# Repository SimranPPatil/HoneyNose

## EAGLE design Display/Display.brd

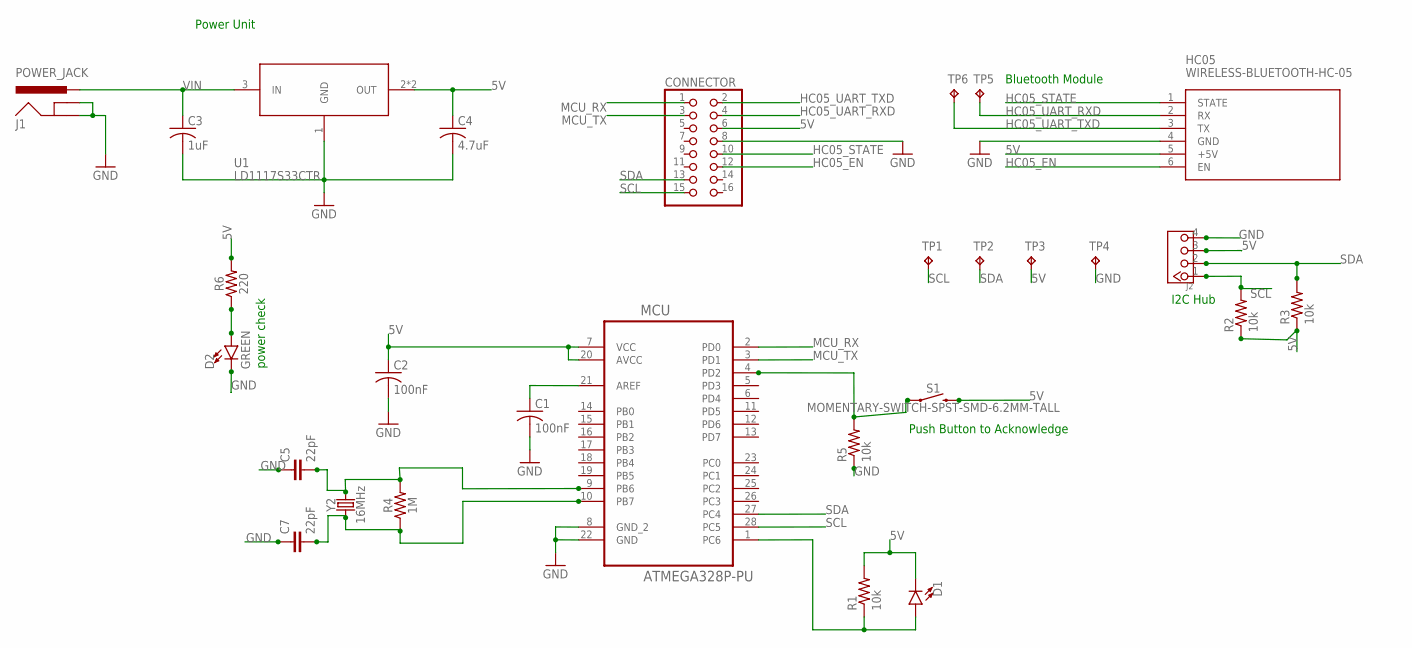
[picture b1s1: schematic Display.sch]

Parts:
C1, C2: 100nF; C0603
C3: 1uF; C0603
C4: 4.7uF; C0603
C5, C7: 22pF; 0603
CONNECTOR: PINHD-2X8; 2X08
D1: LED1206; LED-1206
D2: GREEN; LED-1206
HC05: WIRELESS-BLUETOOTH-HC-05
J1: POWER_JACK; POWER_JACK_PTH
J2: TWIG-4P-2.0; 4P-2.0-W/O-BUCKLE
MCU: ATMEGA328P-PU; DIP254P762X457-28
R1, R2, R3, R5: 10k; R0603
R4: 1M; 0603
R6: 220; 0603
S1: MOMENTARY-SWITCH-SPST-SMD-6.2MM-TALL; TACTILE_SWITCH_SMD_6.2MM_TALL
TP1, TP2, TP3, TP4, TP5, TP6: TPTP20R; TP20R
U1: LD1117S33CTR; SOT223
Y2: 16MHz; HC49US

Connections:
5V: C2.1, C4.1, CONNECTOR.6, D1.C, HC05.5 (+5V), J2.3, MCU.7 (VCC), MCU.20 (AVCC), R1.2, R2.1, R3.1, R6.2, S1.B2 (2), TP3.TP, U1.2 (OUT), U1.4 (OUT)
GND: C1.2, C2.2, C3.2, C4.2, C5.1, C7.1, CONNECTOR.8, D2.C, HC05.4 (GND), J1.GND, J1.GNDBREAK, J2.4, MCU.8 (GND_2), MCU.22 (GND), R5.1, TP4.TP, U1.1 (GND)
HC05_EN: CONNECTOR.12, HC05.6 (EN)
HC05_STATE: CONNECTOR.10, HC05.1 (STATE)
HC05_UART_RXD: CONNECTOR.4, HC05.2 (RX), TP5.TP
HC05_UART_TXD: CONNECTOR.2, HC05.3 (TX), TP6.TP
MCU_RX: CONNECTOR.1, MCU.2 (PD0)
MCU_TX: CONNECTOR.3, MCU.3 (PD1)
unnamed: C5.2, MCU.9 (PB6), R4.2, Y2.2
unnamed: C1.1, MCU.21 (AREF)
unnamed: C7.2, MCU.10 (PB7), R4.1, Y2.1
unnamed: D1.A, MCU.1 (PC6), R1.1
unnamed: MCU.4 (PD2), R5.2, S1.A2 (1)
unnamed: D2.A, R6.1
SCL: CONNECTOR.15, J2.1, MCU.28 (PC5), R2.2, TP1.TP
SDA: CONNECTOR.13, J2.2, MCU.27 (PC4), R3.2, TP2.TP
VIN: C3.1, J1.PWR, U1.3 (IN)

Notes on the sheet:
Bluetooth Module
Power Unit
power check
I2C Hub
Push Button to Acknowledge

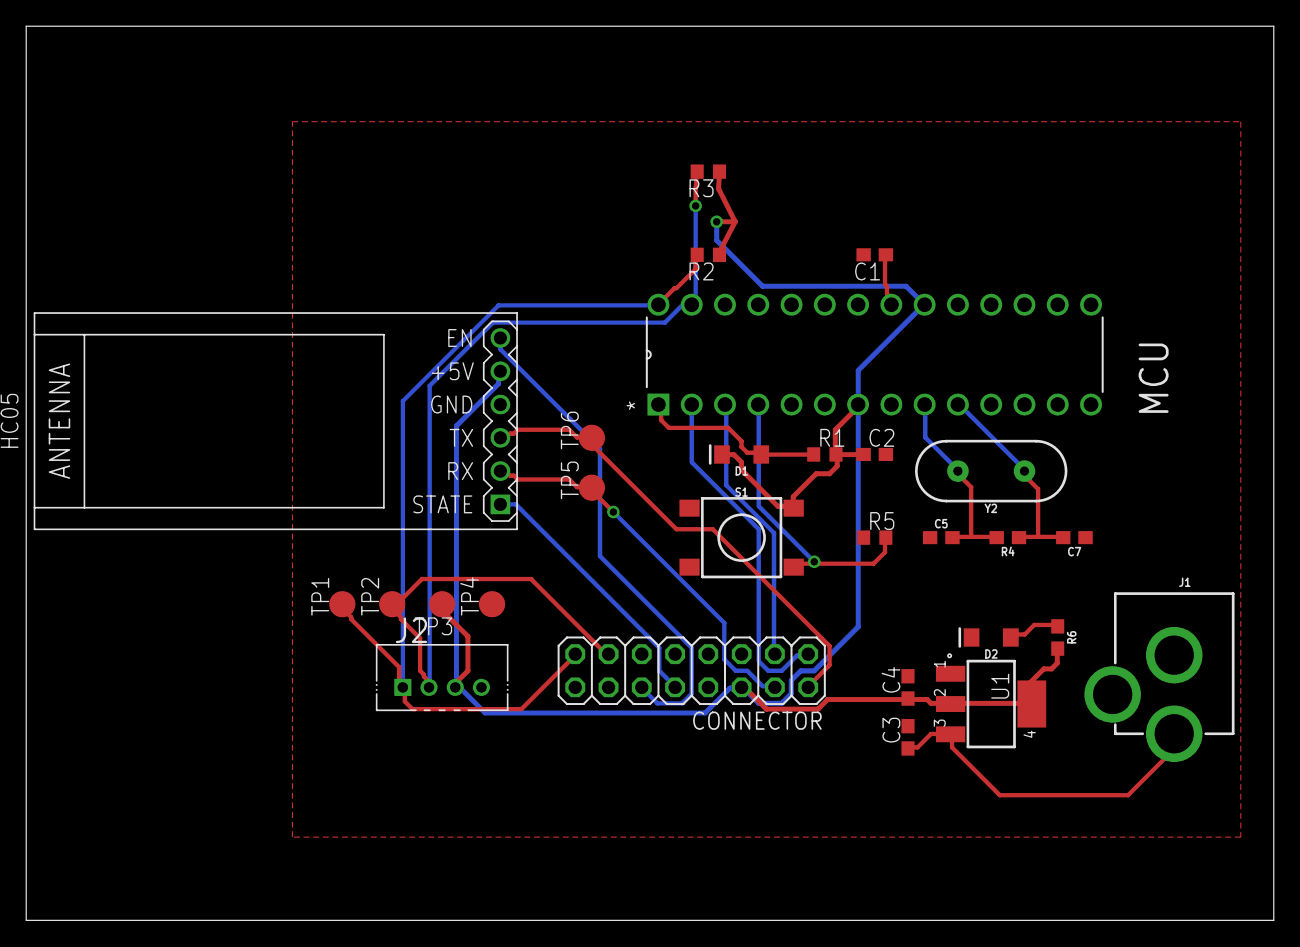
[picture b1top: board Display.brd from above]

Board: 2 copper layers, 95.2 x 68.2 mm, 28 parts (0 on the bottom side), 17 nets.

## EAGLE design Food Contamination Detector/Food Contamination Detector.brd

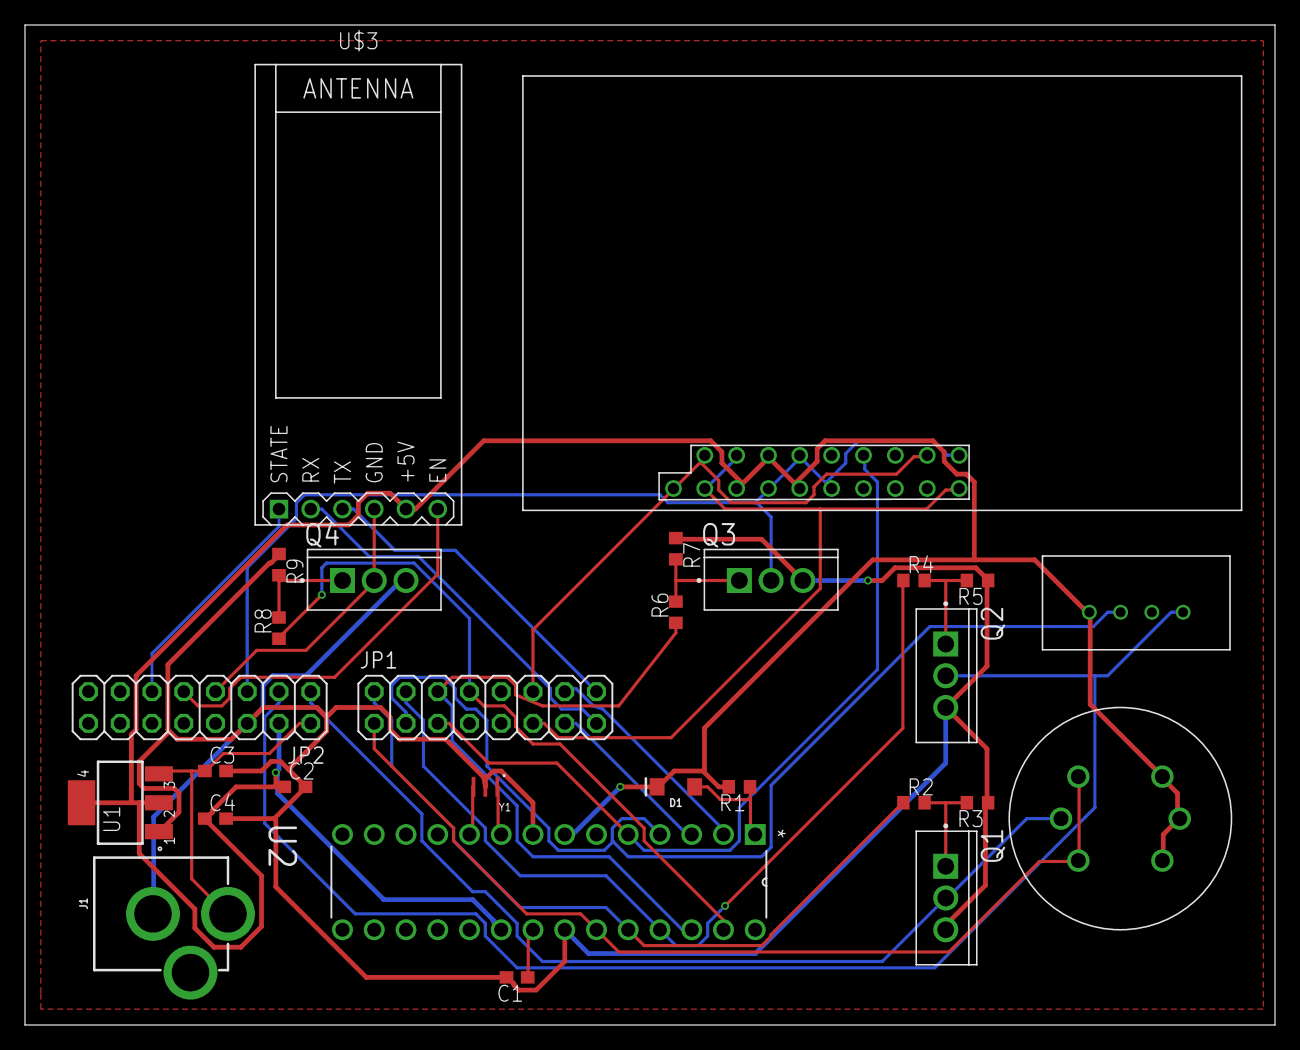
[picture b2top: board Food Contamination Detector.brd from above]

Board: 2 copper layers, 100.0 x 80.0 mm, 28 parts (0 on the bottom side), 30 nets.

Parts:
C1, C2: 100nF; C0603
C3, C4: 0.33uF; C0603
D1: LED-1206
J1: POWER_JACK; POWER_JACK_PTH
JP1, JP2: 2X08
Q1, Q2, Q3, Q4: IRLZ44NPBF; TO254P1067X483X3124-3P
R1, R3, R5, R7, R9: 10k; R0603
R2, R4, R6, R8: 10; R0603
U1: LD1117S33CTR; SOT223
U2: ATMEGA328P-PU; DIP254P762X457-28
U$1: DHT22
U$2: MHZ14; MH-Z14
U$3: WIRELESS-BLUETOOTH-HC-05
U$4: TGS822
Y1: CSTCE16M0V53-R0; OSC_CSTCE16M0V53-R0

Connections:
5V: C2.1, C4.1, D1.C, JP2.4, R1.2, U1.2, U1.4, U2.7, U2.20, U$1.1, U$2.1, U$2.15, U$2.17, U$3.5, U$4.1, U$4.2, U$4.3
DHT22_DATA: JP1.3, U2.4, U$1.2
DHT22_SWITCH: JP2.3, Q2.2, U$1.4
DHT22_SWITCH_IN: JP1.4, R4.1, U2.25
GND: C1.2, C2.2, C3.2, C4.2, J1.GND, JP2.6, Q1.3, Q2.3, Q3.3, Q4.3, R3.1, R5.1, R7.1, R9.1, U1.1, U2.8, U2.22, Y1.2
HC05_EN: JP2.9, U$3.6
HC05_STATE: JP2.11, U$3.1
HC05_SWITCH: JP2.7, Q4.2, U$3.4
HC05_SWITCH_IN: JP1.8, R8.1, U2.27
HC05_UART_RXD: JP1.15, U$3.2
HC05_UART_TXD: JP1.16, U$3.3
MCU_RXD: JP1.13, U2.3
MCU_TXD: JP1.14, U2.2
MHZ14_PWM: JP1.5, U2.5, U$2.6
MHZ14_SWITCH: JP2.5, Q3.2, U$2.2, U$2.3, U$2.12, U$2.16
MHZ14_SWITCH_IN: JP1.6, R6.1, U2.26
MHZ14_UART_RXD: JP1.11, U$2.11, U$2.14, U$2.18
MHZ14_UART_TXD: JP1.12, U$2.10, U$2.13, U$2.19
unnamed: U2.9, Y1.1
unnamed: C1.1, U2.21
unnamed: U2.10, Y1.3
unnamed: D1.A, R1.1, U2.1
unnamed: Q2.1, R4.2, R5.2
unnamed: Q1.1, R2.2, R3.2
unnamed: Q3.1, R6.2, R7.2
unnamed: Q4.1, R8.2, R9.2
TGS822_SWITCH: JP2.1, Q1.2, U$4.5
TGS822_SWITCH_IN: JP1.2, R2.1, U2.24
TGS822_VLR: JP1.1, U2.23, U$4.4, U$4.6
VIN: C3.1, J1.PWR, JP2.2, U1.3

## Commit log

2018-05-30 Senior Design Project
    Cumulative Commit

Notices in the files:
parts and their libraries:
SparkFun-LED: Licensing: Creative Commons ShareAlike 4.0 International - https://creativecommons.org/licenses/by-sa/4.0
diy-modules: Released under the Creative Commons Attribution 4.0 International License: http://creativecommons.org/licenses/by/4.0
